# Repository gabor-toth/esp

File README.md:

Links:
  * https://docs.espressif.com/projects/esp-idf/en/latest/esp32/get-started/linux-macos-setup.html#get-started-first-steps
  * https://github.com/espressif/idf-eclipse-plugin/blob/master/README.md#GettingStarted
  * https://docs.espressif.com/projects/esp-idf/en/v5.0/esp32s2/hw-reference/chip-series-comparison.html

Install
=======

```
sudo apt -y install bison ccache cmake curl dfu-util flex gperf libffi-dev libssl-dev libusb-1.0-0 
sudo apt -y install ninja-build python3 python-is-python3 python3-pip python3-setuptools python3-venv
#sudo apt-get install git wget 
#sudo apt-mark auto libusb-1.0-0 python3 python3-setuptools wget 
```

```
cd ~/own/projects
git clone --recursive https://github.com/espressif/esp-idf.git
cd esp-idf
./install.sh esp32 esp32s2
```

LVGL
----

 * https://github.com/lvgl/lv_port_esp32
 
```
cd esp-idf

git submodule add https://github.com/lvgl/lvgl.git components/lvgl
pushd components/lvgl
git checkout release/v8.3
popd

git submodule add https://github.com/lvgl/lvgl_esp32_drivers.git components/lvgl_esp32_drivers
```

NMEA2000
--------

In menuconfig check "Enable C++ extension" before adding the component

```
mkdir -p components
cd components
git submodule add https://github.com/ttlappalainen/NMEA2000
```

NPM
---

- https://github.com/nvm-sh/nvm

```
curl -o- https://raw.githubusercontent.com/nvm-sh/nvm/v0.40.3/install.sh | bash
# run it on a new terminal
nvm install 22 --save
```

NG
--

```
cd ~/projects/ecp/ontozo/frontend
npm install
npm link @angular/cli
```

Upgrade
=======

Upgrade esp-idf
---------------

```
pushd ../../esp-idf
git pull
git checkout v5.1.2
git submodule update --init --recursive
rm -rf $HOME/.espressif/
./install.sh esp32 esp32s2
. ./export.sh
cd tools
./idf_tools.py install cmake install-python-env
popd
```

Upgrade project in command line
-------------------------------

```
idf.py fullclean
idf.py menuconfig
idf.py build
```

Upgrade project in CLion
------------------------

  * ``echo $PATH``
  * Change IDF_PATH and PATH in CLion
  * File/Reload CMake project

Compile & more
==============

init.sh does this
```
. ~/own/projects/esp-idf/export.sh
```

Find out device

```
$ l /dev/ttyUSB*
crw-rw---- 1 root dialout 188, 0 ápr    5 20:01 /dev/ttyUSB0
sudo usermod -a -G dialout gabor
```

If there's no ttyUSB0
```
sudo apt remove brltty
```

New project
-----------

Copy init.sh, run it

```
. ./init.sh

idf.py set-target esp32s2
idf.py menuconfig
idf.py -p /dev/ttyUSB0 flash -b 3000000 monitor
```

In CLion
  * File, Open
  * CMakeLists.txt

Change target 
-------------

```
idf.py set-target esp32s2
rm -rf cmake-build-debug/
idf.py fullclean
```

Reload CMake project in CLion

Add managed components

```
idf.py add-dependency espressif/mdns
idf.py add-dependency espressif/mpu6050
idf.py add-dependency espressif/esp_websocket_client
idf.py build
```

Git
===

Use different SSL private key

```
export GIT_SSH_COMMAND="ssh -i $HOME/.ssh/id_gabtoth -o IdentitiesOnly=yes"
```

CLion
=====

CMake environment (Settings / Build, Execution, Deployment / CMake / Environment)

```
IDF_PATH=/home/gabor/projects/esp/esp-idf;PATH=home/gabor/projects/esp/esp-idf/components/espcoredump:/home/gabor/projects/esp/esp-idf/components/partition_table:/home/gabor/projects/esp/esp-idf/components/app_update:/home/gabor/.espressif/tools/xtensa-esp-elf-gdb/14.2_20240403/xtensa-esp-elf-gdb/bin:/home/gabor/.espressif/tools/xtensa-esp-elf/esp-14.2.0_20241119/xtensa-esp-elf/bin:/home/gabor/.espressif/tools/riscv32-esp-elf/esp-14.2.0_20241119/riscv32-esp-elf/bin:/home/gabor/.espressif/tools/esp32ulp-elf/2.38_20240113/esp32ulp-elf/bin:/home/gabor/.espressif/tools/cmake/3.30.2/bin:/home/gabor/.espressif/tools/openocd-esp32/v0.12.0-esp32-20250226/openocd-esp32/bin:/home/gabor/.espressif/python_env/idf5.4_py3.12_env/bin:/home/gabor/projects/esp/esp-idf/tools:/usr/local/sbin:/usr/local/bin:/usr/sbin:/usr/bin:/sbin:/bin:/usr/games:/usr/local/games:/snap/bin:/snap/bin
```

Windows
-------

```
[Environment]::GetEnvironmentVariable("IDF_PATH")
$Env:Path
python C:\Espressif\frameworks\esp-idf-v5.2.1-2\tools\idf_tools.py install-python-env
```

Something else

```
PATH += /home/tothg/.espressif/tools/xtensa-esp32-elf/esp-2021r2-patch3-8.4.0/xtensa-esp32-elf/bin:/home/tothg/.espressif/tools/xtensa-clang/12.0.1-d9341b81fc/xtensa-esp32-elf-clang/bin:/home/tothg/.espressif/tools/esp32ulp-elf/2.28.51-esp-20191205/esp32ulp-elf-binutils/bin:/home/tothg/.espressif/tools/cmake/3.20.3/bin:/home/tothg/.espressif/tools/openocd-esp32/v0.11.0-esp32-20211220/openocd-esp32/bin:/home/tothg/.espressif/tools/ninja/1.10.2/:/home/tothg/.espressif/python_env/idf5.0_py3.8_env/bin:/home/gabor/projects/esp-idf/tools:
IDF_PATH = /home/gabor/projects/esp-idf
```

USB on Windows
--------------

- https://blog.manzelseet.com/fixing-cp2102-with-custom-vidpid.html
- https://community.silabs.com/s/article/downloading-cp210x-drivers-from-windows-update?language=en_US
  The PIDs that must be programmed to the CP210x device are listed below: 0x10C4 0xEA63
- https://github.com/DiUS/cp210x-cfg/blob/master/README.md
- https://blog.manzelseet.com/fixing-cp2102-with-custom-vidpid.html
- https://community.silabs.com/s/question/0D51M00007xeNnTSAU/an721-cp21xxcustomizationutilityexe-not-found?language=en_US

Hardware
========

Display
-------

  * https://electropeak.com/learn/interfacing-2-8-inch-tft-lcd-touch-screen-with-esp32/
  * http://www.lcdwiki.com/2.8inch_SPI_Module_ILI9341_SKU:MSP2807

KiCad
=====

* search parts: https://componentsearchengine.com/
* library loader: https://componentsearchengine.com/ga/libraryLoaderSetup.php?flow=ll

links
* https://ms.componentsearchengine.com/library/kicad

TODO
====

fatal: remote error: upload-pack: not our ref 04b38e68fdf662cc866fca628e3e67a9714209d1
fatal: remote error: upload-pack: not our ref e1ba2bd2f61cd81c16b31b09772967fbfd72edd2
fatal: remote error: upload-pack: not our ref 11aa66e7f39c9402039882acb14a993e390f8893
fatal: remote error: upload-pack: not our ref 848df55b08dcdad33c7dd9dbc25deacd2fc5e489
fatal: remote error: upload-pack: not our ref 30e5c4f95bff1a17e06ce1042a165b0aa2bc4ca5
Errors during submodule fetch:
	components/lwip/lwip
	components/esp_wifi/lib
	components/bt/controller/lib_esp32h2/esp32h2-bt-lib
	components/bt/controller/lib_esp32c6/esp32c6-bt-lib
	components/bt/controller/lib_esp32c2/esp32c2-bt-lib

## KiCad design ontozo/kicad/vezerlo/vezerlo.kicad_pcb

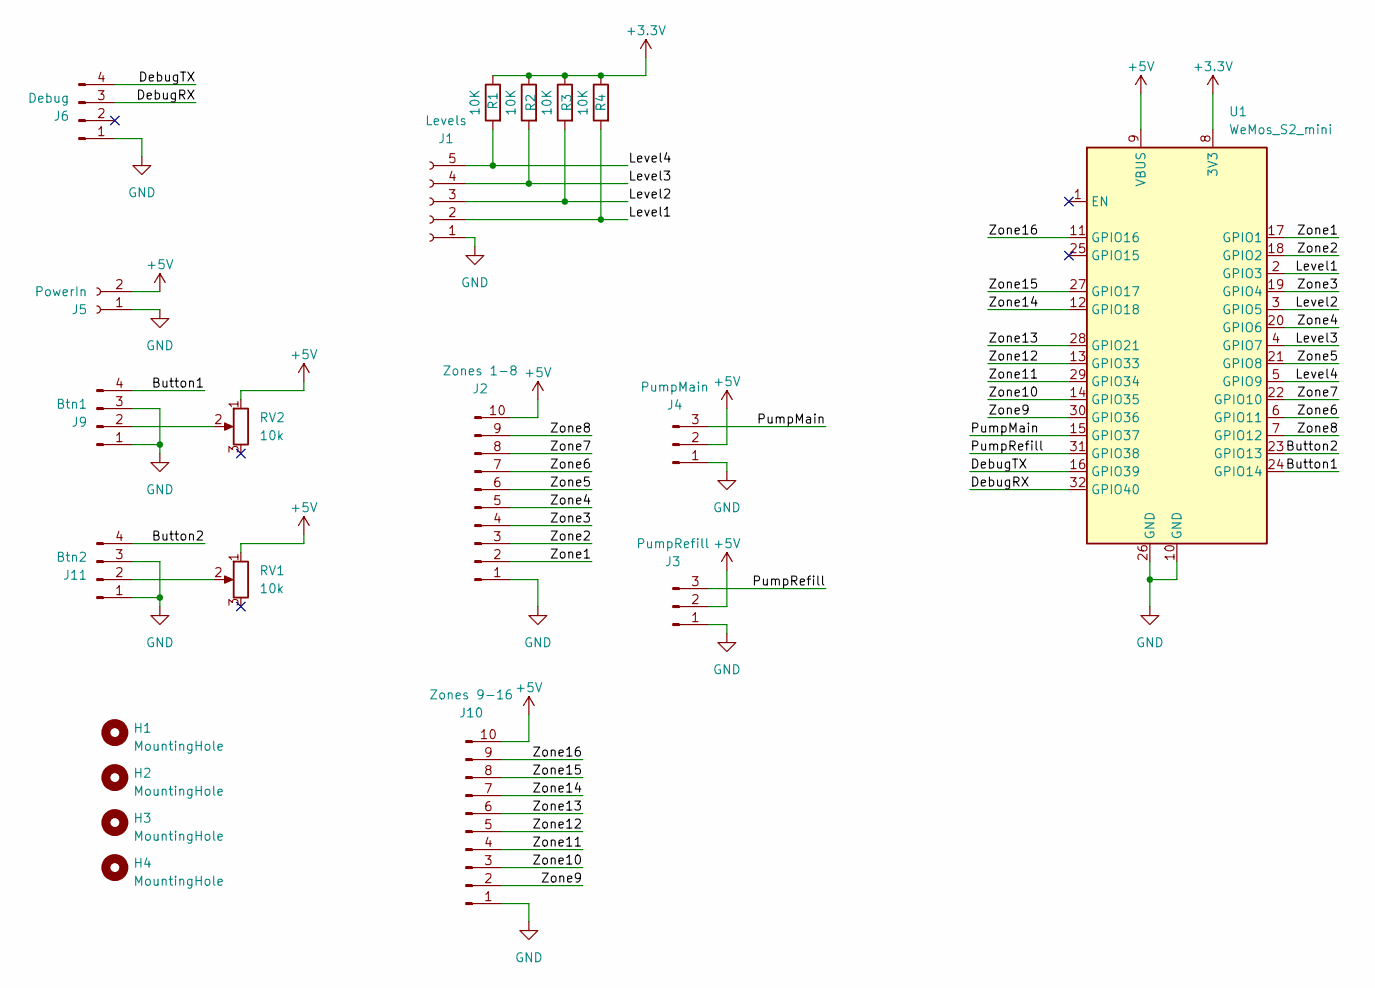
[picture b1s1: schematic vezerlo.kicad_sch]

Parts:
H1, H2, H3, H4: MountingHole; MountingHole_3.2mm_M3
J1: Levels; TerminalBlock_Phoenix_MKDS-1,5-5-5.08_1x05_P5.08mm_Horizont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
J2: Zones 1-8; PinHeader_1x10_P2.54mm_Vertical
J3: PumpRefill; PinHeader_1x03_P2.54mm_Vertical
J4: PumpMain; PinHeader_1x03_P2.54mm_Vertical
J5: PowerIn; TerminalBlock_Phoenix_MKDS-1,5-2-5.08_1x02_P5.08mm_Horizont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
J6: Debug; PinHeader_1x04_P2.54mm_Vertical
J9: Btn1; TerminalBlock_Phoenix_MKDS-1,5-4-5.08_1x04_P5.08mm_Horizont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
J10: Zones 9-16; PinHeader_1x10_P2.54mm_Vertical
J11: Btn2; TerminalBlock_Phoenix_MKDS-1,5-4-5.08_1x04_P5.08mm_Horizont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
R1, R2, R3, R4: 10K; R_Axial_DIN0207_L6.3mm_D2.5mm_P7.62mm_Horizontal
RV1, RV2: 10k; Potentiometer_Bourns_3386P_Vertical
U1: WeMos_S2_mini; WEMOS_S2_mini_gogo

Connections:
+3.3V: R1.1, R2.1, R3.1, R4.1, U1.8 (3V3)
+5V: J2.10, J3.2, J4.2, J5.2, J10.10, RV1.1, RV2.1, U1.9 (VBUS)
/Button1: J9.4, U1.24 (GPIO14)
/Button2: J11.4, U1.23 (GPIO13)
/DebugRX: J6.3, U1.32 (GPIO40)
/DebugTX: J6.4, U1.16 (GPIO39)
/Level1: J1.2, R4.2, U1.2 (GPIO3)
/Level2: J1.3, R3.2, U1.3 (GPIO5)
/Level3: J1.4, R2.2, U1.4 (GPIO7)
/Level4: J1.5, R1.2, U1.5 (GPIO9)
/PumpMain: J4.3, U1.15 (GPIO37)
/PumpRefill: J3.3, U1.31 (GPIO38)
/Zone1: J2.2, U1.17 (GPIO1)
/Zone2: J2.3, U1.18 (GPIO2)
/Zone3: J2.4, U1.19 (GPIO4)
/Zone4: J2.5, U1.20 (GPIO6)
/Zone5: J2.6, U1.21 (GPIO8)
/Zone6: J2.7, U1.6 (GPIO11)
/Zone7: J2.8, U1.22 (GPIO10)
/Zone8: J2.9, U1.7 (GPIO12)
/Zone9: J10.2, U1.30 (GPIO36)
/Zone10: J10.3, U1.14 (GPIO35)
/Zone11: J10.4, U1.29 (GPIO34)
/Zone12: J10.5, U1.13 (GPIO33)
/Zone13: J10.6, U1.28 (GPIO21)
/Zone14: J10.7, U1.12 (GPIO18)
/Zone15: J10.8, U1.27 (GPIO17)
/Zone16: J10.9, U1.11 (GPIO16)
GND: J1.1, J2.1, J3.1, J4.1, J5.1, J6.1, J9.1, J9.3, J10.1, J11.1, J11.3, U1.10 (GND), U1.26 (GND)
unnamed: J9.2, RV2.2
unnamed: J11.2, RV1.2

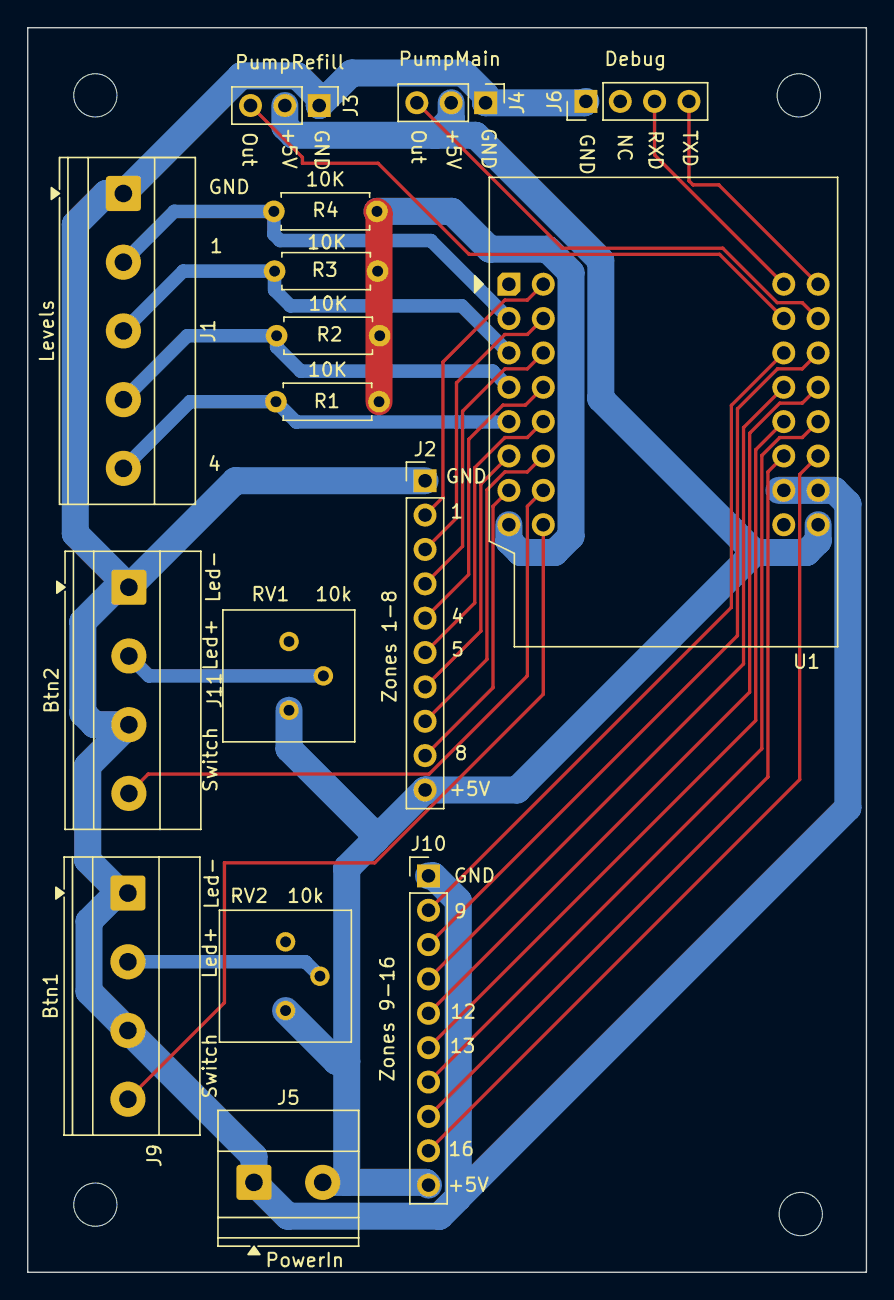
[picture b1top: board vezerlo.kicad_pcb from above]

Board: 2 copper layers, 62.0 x 92.0 mm, 20 parts (0 on the bottom side), 31 nets.

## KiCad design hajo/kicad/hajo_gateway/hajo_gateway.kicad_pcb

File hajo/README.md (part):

# Signal K

- https://signalk.org/installation.html
    - https://demo.signalk.org/@signalk/instrumentpanel/
- https://github.com/SignalK/signalk-server#how-to-get-signal-k-server
- https://github.com/SignalK/signalk-server/blob/master/docker/README.md#quickstart

# Raspberry PI

## Install

### System

- download Raspberry PI Imager from here: https://www.raspberrypi.com/software/
- choose 'Raspberry PI OS (other)', then choose 'OS Lite (64 bit)'
- (which will download an image from
  here https://www.raspberrypi.com/software/operating-systems/#raspberry-pi-os-64-bit)
- select target SD card and write
- put SD card into PI, boot with HDMI and keyboard connected
- select Hungarian layout and normal keyboard
- set hostname to 'signalk'
- create user 'signalk' with password 'signalk'
- login with those credentials
- set up ssh server

```shell
sudo raspi-config
```

- then go to menu 3 'Interfaces' and I1 'SSH'
- and enable it
- connect from your pc

```shell
ssh signalk@192.168.72.191
```

- and continue in ssh

```shell
mkdir -p .ssh
chmod 700 .ssh/
echo 'ssh-ed25519 AAAAC3NzaC1lZDI1NTE5AAAAIKcyI/bADRtxOoJ1hDOtbntHil+7zQbVbTIEuEyCPMNb gabor.toth@p92.hu' > .ssh/authorized_keys

sudo su
apt -y update
apt -y upgrade
apt -y install lsb-release traceroute vim
sed -i 's/raspberrypi/solpi/' /etc/hosts
hostnamectl set-hostname solpi
sed -i '/history-search/ s/# //' /etc/inputrc
dpkg-reconfigure tzdata
# unattended-upgrades
# dpkg-reconfigure --priority=low unattended-upgrades
# raspi-config
 # ?
exit
exit
```

### Upgrade

Determine current version

```shell
lsb_release -a
cat /etc/debian_version 
```

Upgrade system

```shell
systemctl stop signalk
systemctl stop signalk.socket
systemctl stop shewllinabox

apt update
apt full-upgrade
```

Upgrade firmware

```shell
rpi-update
chmod -x /etc/cron.d/hotspot 
reboot
chmod +x /etc/cron.d/hotspot
```

### Power

- LED & HDMI: https://www.jeffgeerling.com/blogs/jeff-geerling/controlling-pwr-act-leds-raspberry-pi
- https://linuxhint.com/tips-tricks-optimize-power-consumption-raspberry-pi/
- https://raspberrypi.stackexchange.com/questions/114422/what-is-the-minimum-power-required-for-an-rpi-4-in-halt-or-shutdown/114423#114423

TODO: add commands

#### Tweak hardware settings

- https://linuxhint.com/tips-tricks-optimize-power-consumption-raspberry-pi/

```shell
sudo su
vi /boot/firmware/config.txt

# power save stuff
arm_boost=0
dtoverlay=disable-bt
# Turn off Power LED
dtparam=pwr_led_trigger=default-on
dtparam=pwr_led_activelow=off
# Turn off Activity LED
dtparam=act_led_trigger=none
dtparam=act_led_activelow=off
# Turn off Ethernet ACT LED
dtparam=eth_led0=4
# Turn off Ethernet LNK LED
dtparam=eth_led1=4

# clock is not stable below 600
arm_freq_min=600
core_freq_min=100
sdram_freq_min=50
over_voltage_min=0
```

Bluetooth

```shell
systemctl stop bluetooth
systemctl disable bluetooth
```

Startup speed

```shell
systemd-analyze blame
```

### SignalK

Source link?

```shell
sudo su
# install v18 on bookworm (needed for Zero)
apt -y install nodejs npm
# install latest (v22 at the time being)
curl -fsSL https://deb.nodesource.com/setup_20.x | bash -
apt -y install nodejs
# continue for all
apt -y install libnss-mdns avahi-utils libavahi-compat-libdnssd-dev
apt-mark auto libnss-mdns
npm install -g npm@latest
npm install -g --unsafe-perm signalk-server -y # will take a while
signalk-server-setup
# Enter the location to store server configuration: /home/signalk/.signalk
# Enter your vessel name: sol
# Enter your mmsi if you have one: 
# The Signal K default port is 3000
# Port 80 does not require ":3000" in the browser and app interfaces
# Do you want to use port 80? Yes
# Do you want to enable SSL? No

cat >>/etc/systemd/system/signalk.service <<EOF
[Unit]
Wants=network.target
EOF
systemctl daemon-reload
```

For local debugging

```
npm install --unsafe-perm signalk-server -y
./node_modules/.bin/signalk-server-setup
/home/apa/.signalk/signalk-server
#/usr/bin/node --inspect ...
```

#### Canboat

```shell
sudo raspi-config
```

- Interface Options
- Serial Port
- No (login shell)
- Yes (serial)
- Reboot

https://github.com/canboat/canboat/wiki/Building

```shell
sudo apt -y install git
git clone https://github.com/canboat/canboat
# or
git pull
cd canboat
make
sudo make install

sudo usermod -a -G dialout signalk
# log out and in
actisense-serial -d /dev/ttyAMA0
```

- Server
- Data connections
- type: NMEA 2000, id: n2k
- source: Actisense NGT-1 (canboat), port /dev/ttyAMA0, baud 115200

#### Dashboard

- go to http://192.168.72.191/
- create an admin account admin/signalk
- login
- Install from Appstore
    - mandatory
        - @mxtommy/kip (https://github.com/mxtommy/Kip)
        - @signalk/freeboard-sk
        - @signalk/charts-plugin
        - @signalk/course-provider
        - @signalk/set-system-time
        - signalk-alarm-silencer
        - signalk-derived-data (https://github.com/SignalK/signalk-derived-data/blob/master/README.md)
        - signalk-racing-calculator
        - signalk-generic-pgn-parser
        - optional
            - signalk-fixed-position
            - @signalk/signalk-autopilot
            - rest-provider-signalk (https://www.npmjs.com/package/rest-provider-signalk)
- Derived data
    - Engines: main
    - Batteries: 0,1,2
    - Heading: Magnetic Variation
    - Submit
    - Heading: True Heading
    - Course data
        - Course DTG, XTE, BRG, etc
        - Velocity Made Good towards next waypoint
        - Velocity Made Good to wind
    - optional
        - Wind: Wind shift
- Course Data provider
    - GreatCircle
- Setup
    - Server,Settings, Options, mdns enable
    - Save, restart
- Create user kip, set pwd kip, admin or at least r/w
- Link: http://192.168.72.156/@mxtommy/kip
- Copy demo page to local user
    - load demo
    - menu Configuration, Settings,
    - connect to local, don't log in,
    - request token, approve in SignalK (timeout = NEVER)
    - go to Storage tab, save layout to global/default
    - go to SignalK tab, log in with kip/kip
    - go to Storage tab, copy remote global/default to remote user/default
- offline maps
    - see https://pysselilivet.blogspot.com/2021/09/signal-k-charts-offline-online.html
      ```shell
      cd ~/.signalk/charts
      wget https://ftp.gwdg.de/pub/misc/openstreetmap/openseamap/charts/mbtiles/OSM-OpenCPN2-Lake_Balaton.mbtiles
      ```
    - click Submit in "Signal K Charts" plugin
    - check results: http://192.168.72.156/signalk/v2/api/resources/charts
- heartbneat
    - configure signalk-generic-pgn-parser
- todo
    - self.electrical.batteries.1.voltage

### Amend PGNs in Signalk

Check whether PGN definition is there

- /usr/lib/node_modules/signalk-server/node_modules/@canboat/pgns/canboat.json
- /usr/lib/node_modules/signalk-server/node_modules/@canboat/pgns/pgns.json
- /usr/lib/node_modules/signalk-server/node_modules/@canboat/pgns/canboat.json

Implement mapper here

- /usr/lib/node_modules/signalk-server/node_modules/@signalk/n2k-signalk/n2kMapper.js
- /usr/lib/node_modules/signalk-server/node_modules/@signalk/n2k-signalk/raymarine/index.js
- /usr/lib/node_modules/signalk-server/node_modules/@signalk/n2k-signalk/raymarine/129029.js

### SignalK plugin development

See

- development: https://demo.signalk.org/documentation/develop/plugins/server_plugin.html
- npm link: https://docs.npmjs.com/cli/v9/commands/npm-link

```shell
cd projects/signalk-generic-pgn-parser
sudo npm link
cd ~/.signalk/
npm link signalk-generic-pgn-parser
```

### Wifi AP

On Debian 12 (Bookworm), see https://raspberrytips.com/access-point-setup-raspberry-pi/

```shell
raspi-config
  Localization, Wifi country, HU, Finish
nmcli con add con-name hotspot ifname wlan0 type wifi ssid "sol"
nmcli con modify hotspot ipv4.method shared ipv4.address 192.168.77.1/24
nmcli con modify hotspot wifi-sec.key-mgmt wpa-psk
nmcli con modify hotspot wifi-sec.psk "SoL37695"
nmcli con modify hotspot 802-11-wireless.mode ap 802-11-wireless.band bg 802-11-wireless.channel 2 ipv4.method shared
nmcli con modify hotspot 802-11-wireless.channel 7
nmcli con modify hotspot 802-11-wireless-security.proto rsn

nmcli connection down hotspot
nmcli connection up hotspot
```

User interface

```shell
nmtui
```

### Wifi station

On Debian 12 (Bookworm):

```shell
nmcli dev show wlan0
nmcli dev wifi list
nmcli connection show

#nmcli dev set wlan1 autoconnect yes
nmcli dev wifi connect TothKiss password ******** ifname wlan0
nmcli dev wifi connect TGA password ******** ifname wlan0
#nmcli connection modify TothKiss connection.autoconnect yes

systemctl restart NetworkManager
```

Turn off Wifi dongle's LED:

- https://github.com/lwfinger/rtl8188eu/issues/82

```shell
echo 0 > /sys/class/leds/rtl8xxxu-usb1-1.4/brightness
```

See

- https://serverfault.com/questions/869857/systemd-how-to-selectively-disable-wpa-supplicant-for-a-specific-wlan-interface
- https://forums.raspberrypi.com/viewtopic.php?t=211853
- https://stackoverflow.com/questions/66514910/enable-predictable-network-interfaces-via-shell-on-raspberry-pi
- https://forums.raspberrypi.com/viewtopic.php?t=198946

### Others

#### Connect to box

```shell
ssh signalk@192.168.72.156
ssh signalk@192.168.77.1
```

#### Wifi Commands

```shell
sudo su
ip link set dev wlan0 down
ip link set dev wlan0 up
iwlist wlan0 scan
vi wpa_supplicant/wpa_supplicant.conf
wpa_supplicant -B -c /etc/wpa_supplicant/wpa_supplicant.conf -i wlan0
wpa_cli terminate -i wlan0
```

## Build

```shell
idf.py -p /dev/ttyUSB0 flash -b 3000000 -DCONFIG_DEVICE_TYPE=GATEWAY -DCONFIG_START_SIMULATOR=y
```

# Local testing

## In Docker

```shell
docker run -d --init  --name signalk-server -p 3000:3000 -v $(pwd):/home/node/.signalk cr.signalk.io/signalk/signalk-server
```

## Local

```shell
sudo apt isntall libavahi-compat-libdnssd-dev
sudo npm install -g mdns
sudo npm install -g signalk-server
```

## Requests

```shell
curl -X GET http://10.128.65.180:3000/signalk
{"endpoints":{"v1":{"version":"2.4.1","
signalk-http":"http://10.128.65.180:3000/signalk/v1/api/","signalk-ws":"ws://10.128.65.180:3000/signalk/v1/stream","signalk-tcp":"tcp://10.128.65.180:8375"}},"server":{"id":"signalk-server-node","version":"2.4.1"}}
```

```shell
wscat -c "ws://10.128.65.180:3000/signalk/v1/stream?subscribe=all"
Connected (press CTRL+C to quit)
< {"name":"signalk-server","version":"2.4.1","self":"vessels.urn:mrn:signalk:uuid:
59e1f1c9-9e32-4340-a1d0-656512c48f0a","roles":["master","main"],"timestamp":"2023-11-22T12:55:47.852Z"}
< {"context":"vessels.urn:mrn:signalk:uuid:59e1f1c9-9e32-4340-a1d0-656512c48f0a","updates":[{"$source":"defaults","
timestamp":"2023-11-22T12:43:36.969Z","
values":[{"path":"","value":{"uuid":"urn:mrn:signalk:uuid:59e1f1c9-9e32-4340-a1d0-656512c48f0a"}}]}]}
```

## Other links

- [Discovery and Connection Establishment](https://signalk.org/specification/1.7.0/doc/connection.html)
- [Streaming API](https://signalk.org/specification/1.7.0/doc/streaming_api.html)

## Service Sniffer

```shell
sudo apt install gssdp-tools

# MDNS
avahi-browse -r -a -t
avahi-browse -r _signalk-ws._tcp
avahi-browse -r _signalk-http._tcp

# SSDP
gssdp-device-sniffer -i docker0
gssdp-device-sniffer -i enp7s0
gssdp-device-sniffer -i wlp0s20f3
```

## URLs

http://192.168.72.182/description.xml
http://192.168.72.182/index.html
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
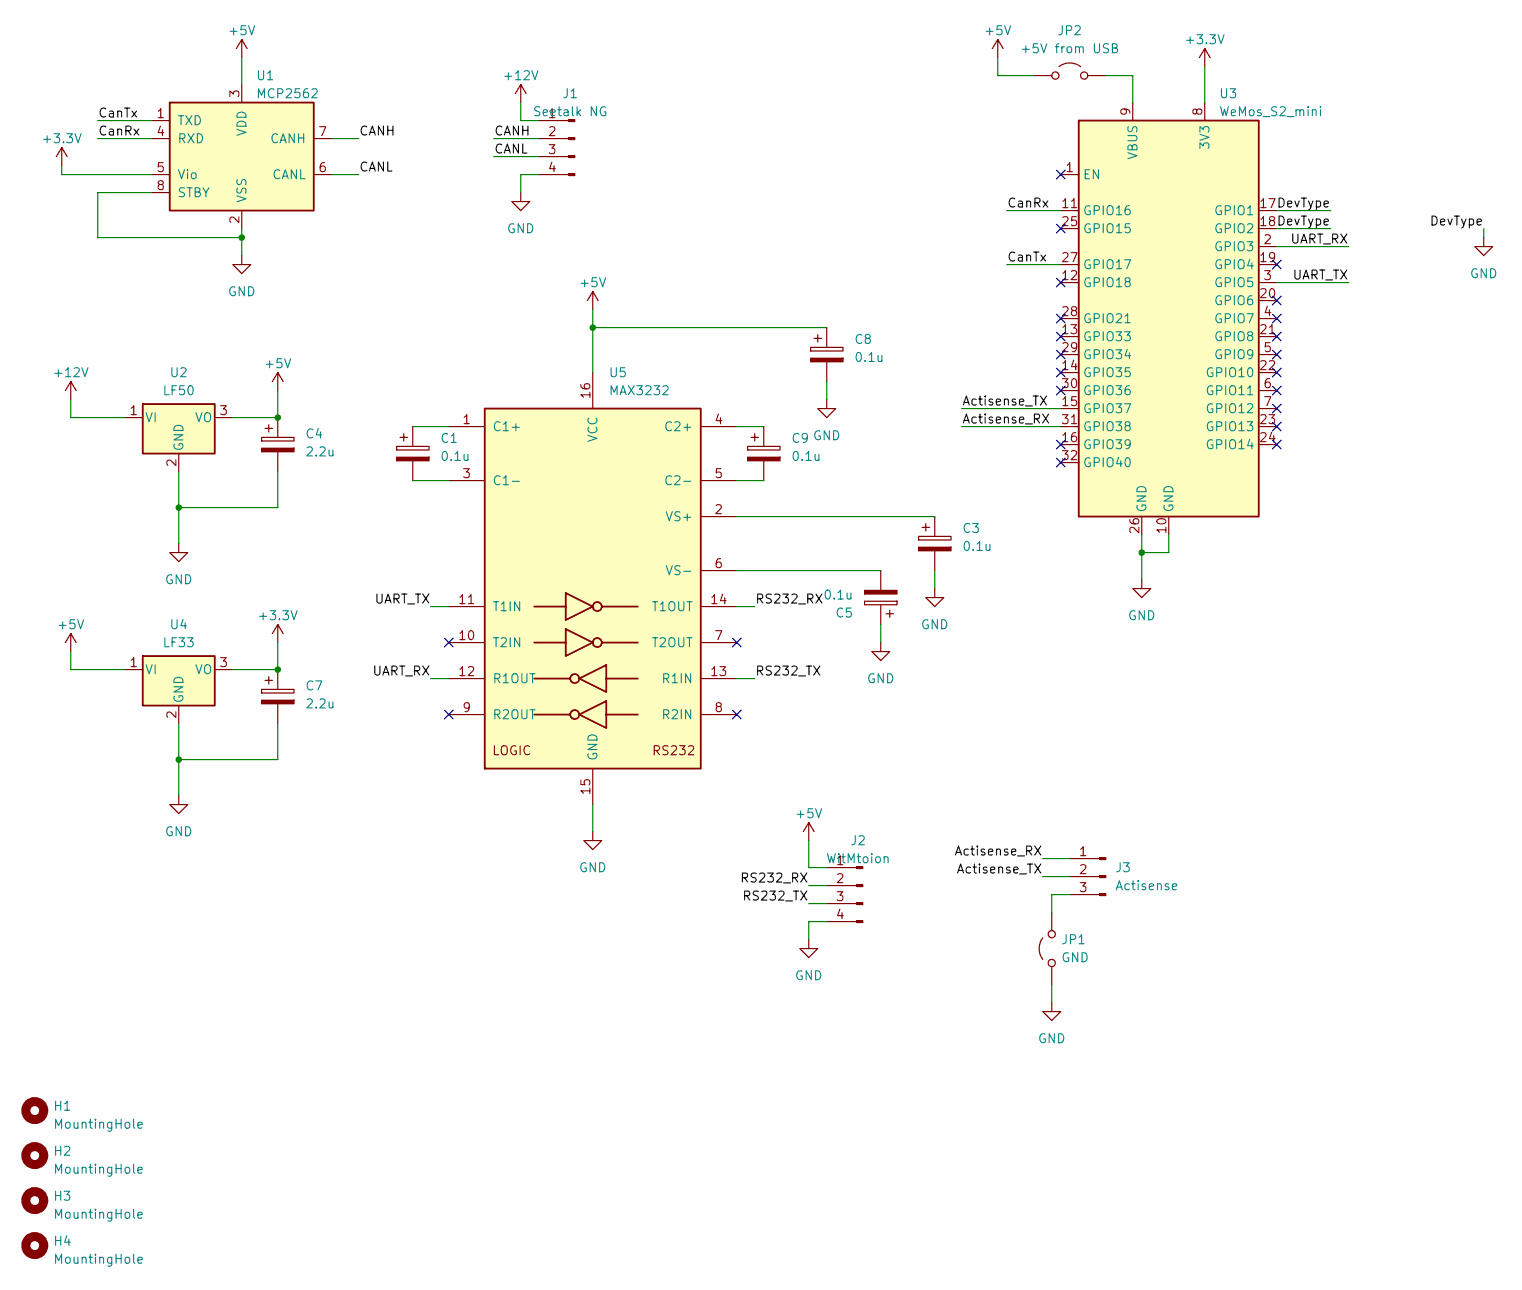
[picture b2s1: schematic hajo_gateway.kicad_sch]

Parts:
C1, C3, C5, C8, C9: 0.1u; CP_Radial_D5.0mm_P2.50mm
C4, C7: 2.2u; CP_Radial_D5.0mm_P2.00mm
H1, H2, H3, H4: MountingHole; MountingHole_3.2mm_M3
J1: Seetalk NG; JST_XA_B04B-XASK-1_1x04_P2.50mm_Vertical
J2: WitMtoion; JST_XA_B04B-XASK-1_1x04_P2.50mm_Vertical
J3: Actisense; JST_XH_B3B-XH-A_1x03_P2.50mm_Vertical
JP1: GND; PinHeader_1x03_P2.54mm_Vertical
JP2: +5V from USB; PinHeader_1x02_P2.54mm_Vertical
U1: MCP2562; DIP-8_W7.62mm_Socket
U2: LF50; TO-220-3_Vertical
U3: WeMos_S2_mini; WEMOS_S2_mini
U4: LF33; TO-220-3_Vertical
U5: MAX3232; DIP-16_W7.62mm_Socket

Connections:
+3.3V: C7.1, U1.5 (Vio), U3.8 (3V3), U4.3 (VO)
+5V: C4.1, C8.1, J2.1, JP2.1 (A), U1.3 (VDD), U2.3 (VO), U4.1 (VI), U5.16 (VCC)
+12V: J1.1, U2.1 (VI)
/Actisense_RX: J3.1, U3.31 (GPIO38)
/Actisense_TX: J3.2, U3.15 (GPIO37)
/CANH: J1.2, U1.7 (CANH)
/CANL: J1.3, U1.6 (CANL)
/CanRx: U1.4 (RXD), U3.11 (GPIO16)
/CanTx: U1.1 (TXD), U3.27 (GPIO17)
/RS232_RX: J2.2, U5.14 (T1OUT)
/RS232_TX: J2.3, U5.13 (R1IN)
/UART_RX: U3.2 (GPIO3), U5.12 (R1OUT)
/UART_TX: U3.3 (GPIO5), U5.11 (T1IN)
GND: C3.2, C4.2, C5.1, C7.2, C8.2, J1.4, J2.4, JP1.1 (A), U1.2 (VSS), U1.8 (STBY), U2.2 (GND), U3.10 (GND), U3.17 (GPIO1), U3.18 (GPIO2), U3.26 (GND), U4.2 (GND), U5.15 (GND)
unnamed: J3.3, JP1.2 (B)
unnamed: JP2.2 (B), U3.9 (VBUS)
unnamed: C1.1, U5.1 (C1+)
unnamed: C1.2, U5.3 (C1-)
unnamed: C9.1, U5.4 (C2+)
unnamed: C9.2, U5.5 (C2-)
unnamed: C3.1, U5.2 (VS+)
unnamed: C5.2, U5.6 (VS-)

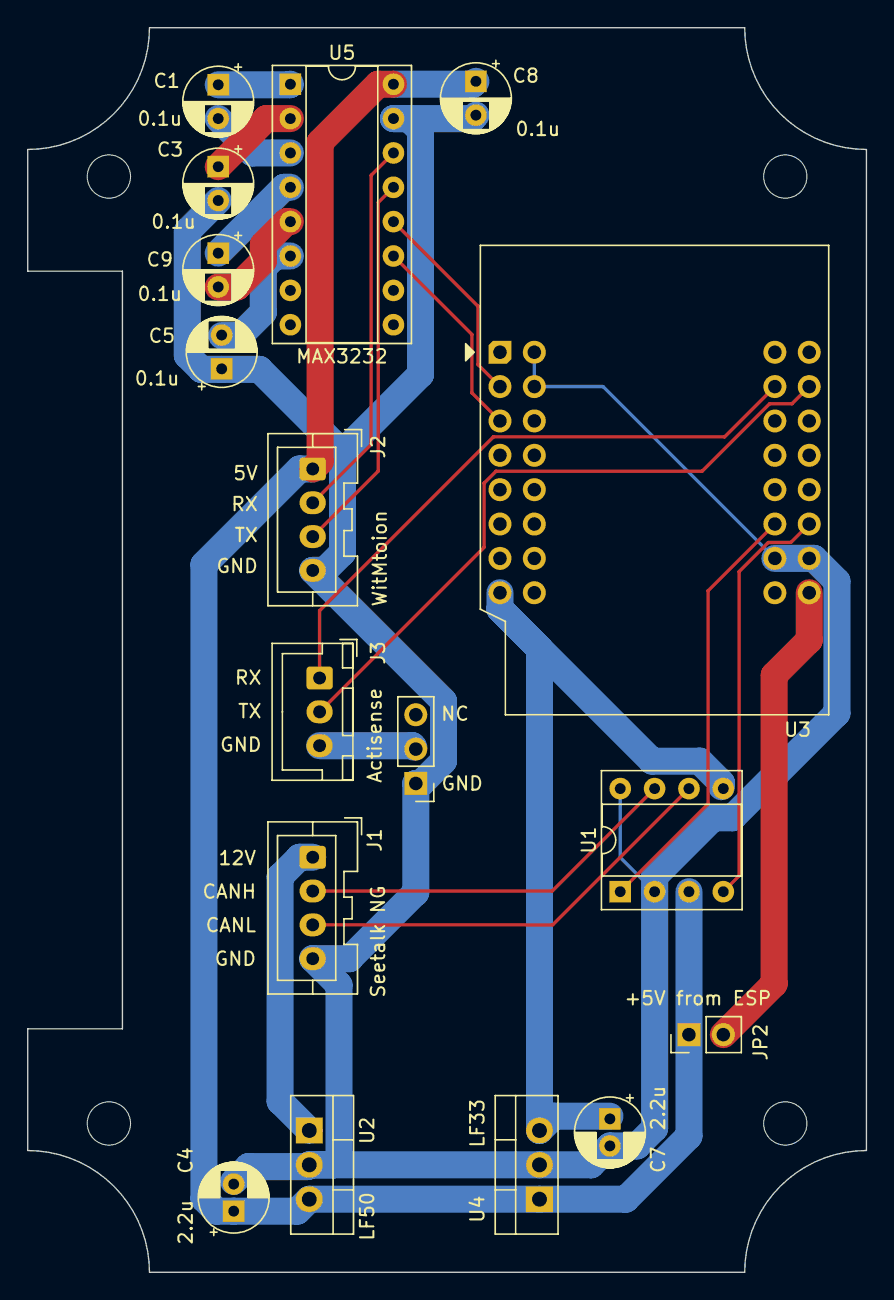
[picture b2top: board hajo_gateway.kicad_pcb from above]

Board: 2 copper layers, 62.0 x 92.0 mm, 21 parts (0 on the bottom side), 22 nets.

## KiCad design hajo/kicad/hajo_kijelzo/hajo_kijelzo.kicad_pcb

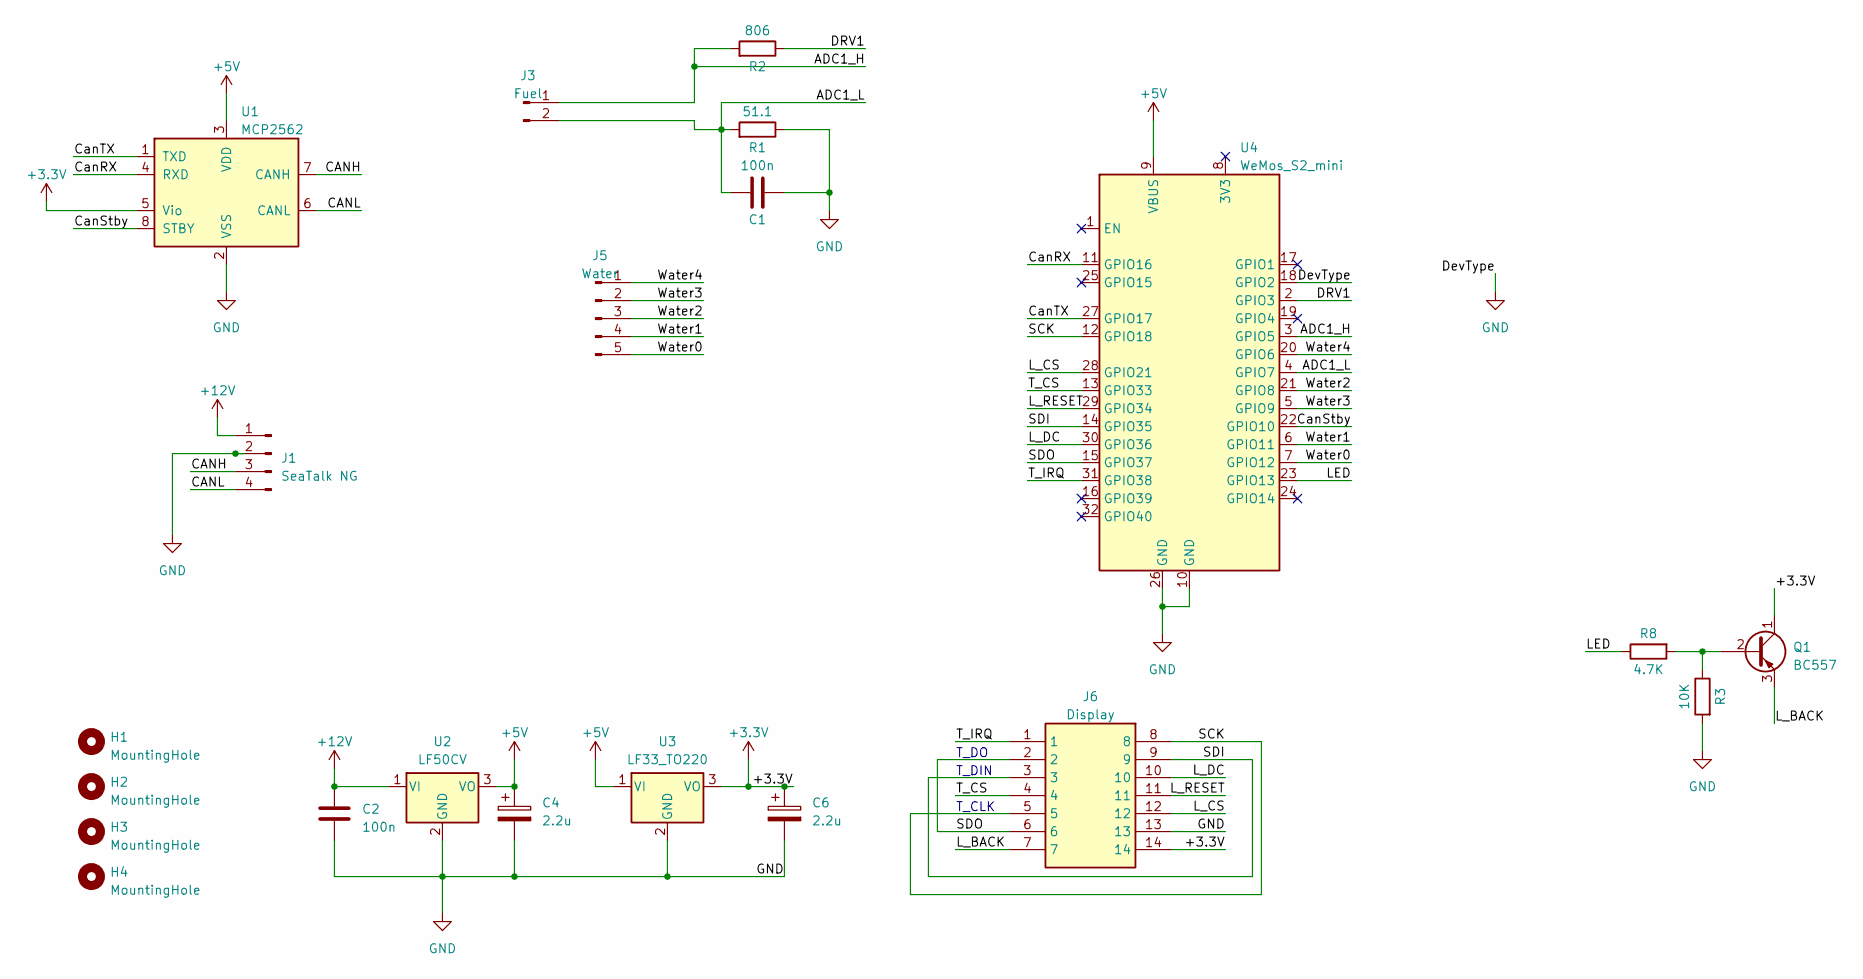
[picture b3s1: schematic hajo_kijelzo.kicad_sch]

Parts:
C1: 100n; C_Rect_L4.0mm_W2.5mm_P2.50mm
C2: 100n; C_Rect_L7.0mm_W2.0mm_P5.00mm
C4, C6: 2.2u; CP_Radial_D5.0mm_P2.00mm
H1, H2, H3, H4: MountingHole; MountingHole_3.2mm_M3
J1: SeaTalk NG; JST_XH_B4B-XH-A_1x04_P2.50mm_Vertical
J3: Fuel; 1821245
J5: Water; 1821274
J6: Display; 1844772; Manufacturer_Part_Number 1844772; Mouser Part Number 651-1844772
Q1: BC557; TO-92_Inline
R1: 51.1; R_Axial_DIN0207_L6.3mm_D2.5mm_P7.62mm_Horizontal
R2: 806; R_Axial_DIN0207_L6.3mm_D2.5mm_P7.62mm_Horizontal
R3: 10K; R_Axial_DIN0207_L6.3mm_D2.5mm_P7.62mm_Horizontal
R8: 4.7K; R_Axial_DIN0207_L6.3mm_D2.5mm_P7.62mm_Horizontal
U1: MCP2562; DIP-8_W7.62mm
U2: LF50CV; TO-220-3_Vertical
U3: LF33_TO220; TO-220-3_Vertical
U4: WeMos_S2_mini; WEMOS_S2_mini

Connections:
+3.3V: C6.1, J6.14, Q1.1 (C), U1.5 (Vio), U3.3 (VO)
+5V: C4.1, U1.3 (VDD), U2.3 (VO), U3.1 (VI), U4.9 (VBUS)
+12V: C2.1, J1.1, U2.1 (VI)
/ADC1_H: J3.1, R2.2, U4.3 (GPIO5)
/ADC1_L: C1.2, J3.2, R1.2, U4.4 (GPIO7)
/CANH: J1.3, U1.7 (CANH)
/CANL: J1.4, U1.6 (CANL)
/CanRX: U1.4 (RXD), U4.11 (GPIO16)
/CanStby: U1.8 (STBY), U4.22 (GPIO10)
/CanTX: U1.1 (TXD), U4.27 (GPIO17)
/DRV1: R2.1, U4.2 (GPIO3)
/LED: R8.1, U4.23 (GPIO13)
/L_BACK: J6.7, Q1.3 (E)
/L_CS: J6.12, U4.28 (GPIO21)
/L_DC: J6.10, U4.30 (GPIO36)
/L_RESET: J6.11, U4.29 (GPIO34)
/SCK: J6.5, J6.8, U4.12 (GPIO18)
/SDI: J6.3, J6.9, U4.14 (GPIO35)
/SDO: J6.2, J6.6, U4.15 (GPIO37)
/T_CS: J6.4, U4.13 (GPIO33)
/T_IRQ: J6.1, U4.31 (GPIO38)
/Water0: J5.5, U4.7 (GPIO12)
/Water1: J5.4, U4.6 (GPIO11)
/Water2: J5.3, U4.21 (GPIO8)
/Water3: J5.2, U4.5 (GPIO9)
/Water4: J5.1, U4.20 (GPIO6)
GND: C1.1, C2.2, C4.2, C6.2, J1.2, J6.13, R1.1, R3.2, U1.2 (VSS), U2.2 (GND), U3.2 (GND), U4.10 (GND), U4.18 (GPIO2), U4.26 (GND)
unnamed: Q1.2 (B), R3.1, R8.2

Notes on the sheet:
T_DO
T_DIN
T_CLK

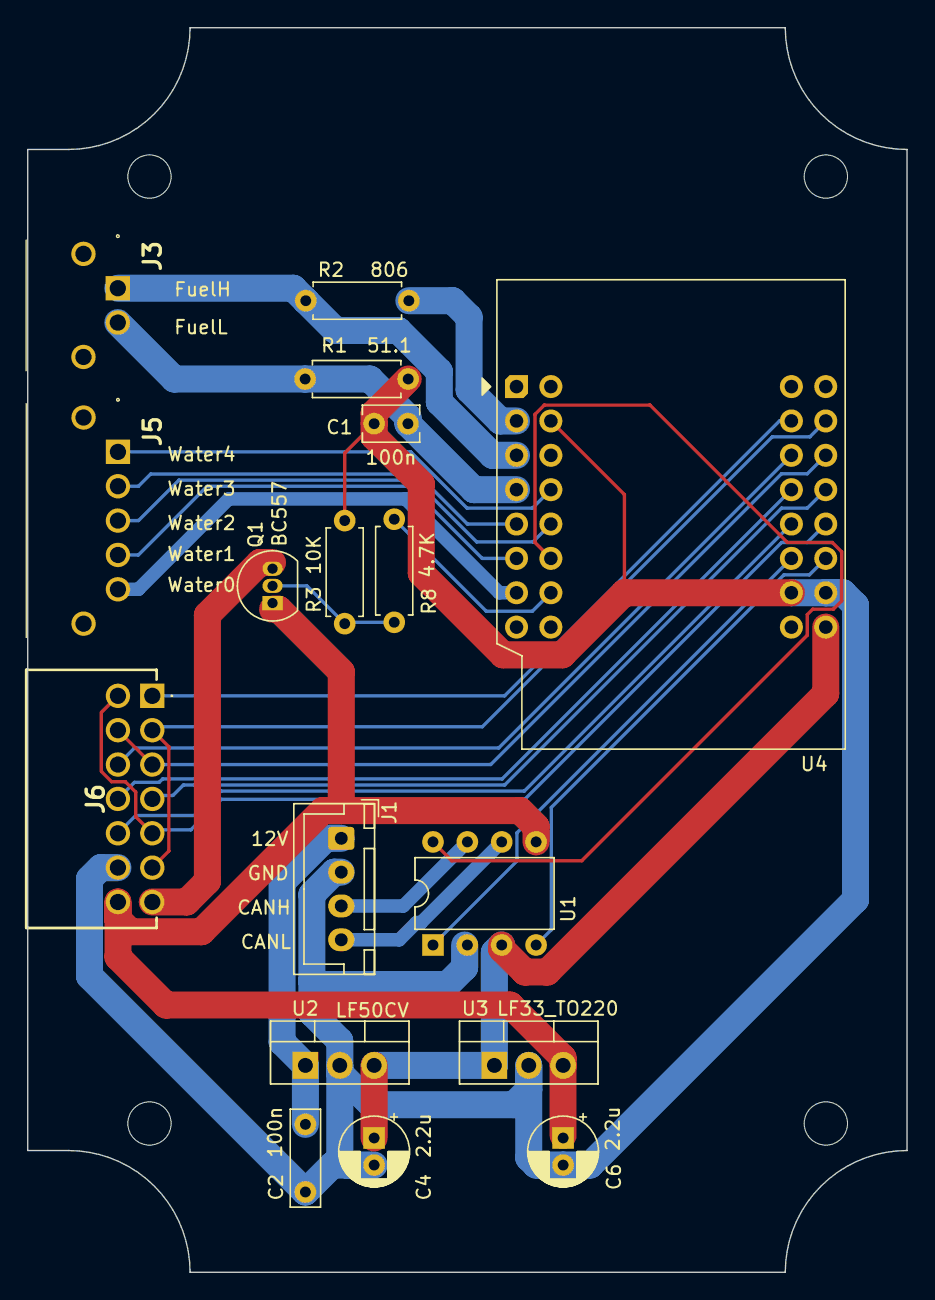
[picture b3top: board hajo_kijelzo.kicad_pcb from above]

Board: 2 copper layers, 65.0 x 92.0 mm, 21 parts (0 on the bottom side), 28 nets.

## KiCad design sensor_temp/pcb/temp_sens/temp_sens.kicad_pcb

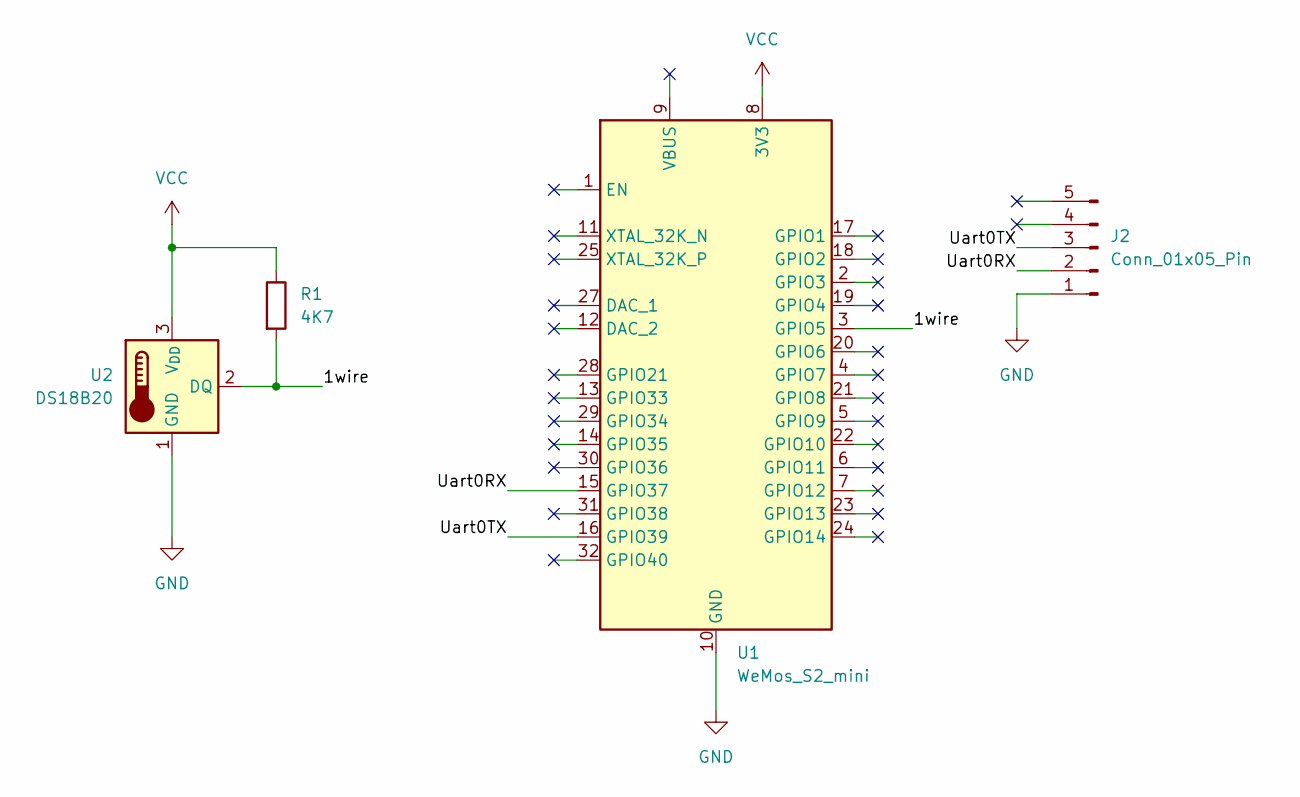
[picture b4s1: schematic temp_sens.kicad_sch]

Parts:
J2: Conn_01x05_Pin; PinHeader_1x05_P2.54mm_Horizontal
R1: 4K7; R_Axial_DIN0207_L6.3mm_D2.5mm_P10.16mm_Horizontal
U1: WeMos_S2_mini; WEMOS_S2_mini_traced
U2: DS18B20; TO-92_Inline

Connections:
/1wire: R1.2, U1.3 (GPIO5), U2.2 (DQ)
/Uart0RX: J2.2, U1.15 (GPIO37)
/Uart0TX: J2.3, U1.16 (GPIO39)
GND: J2.1, U1.10 (GND), U1.26 (GND), U2.1 (GND)
VCC: R1.1, U1.8 (3V3), U2.3 (V_{DD})

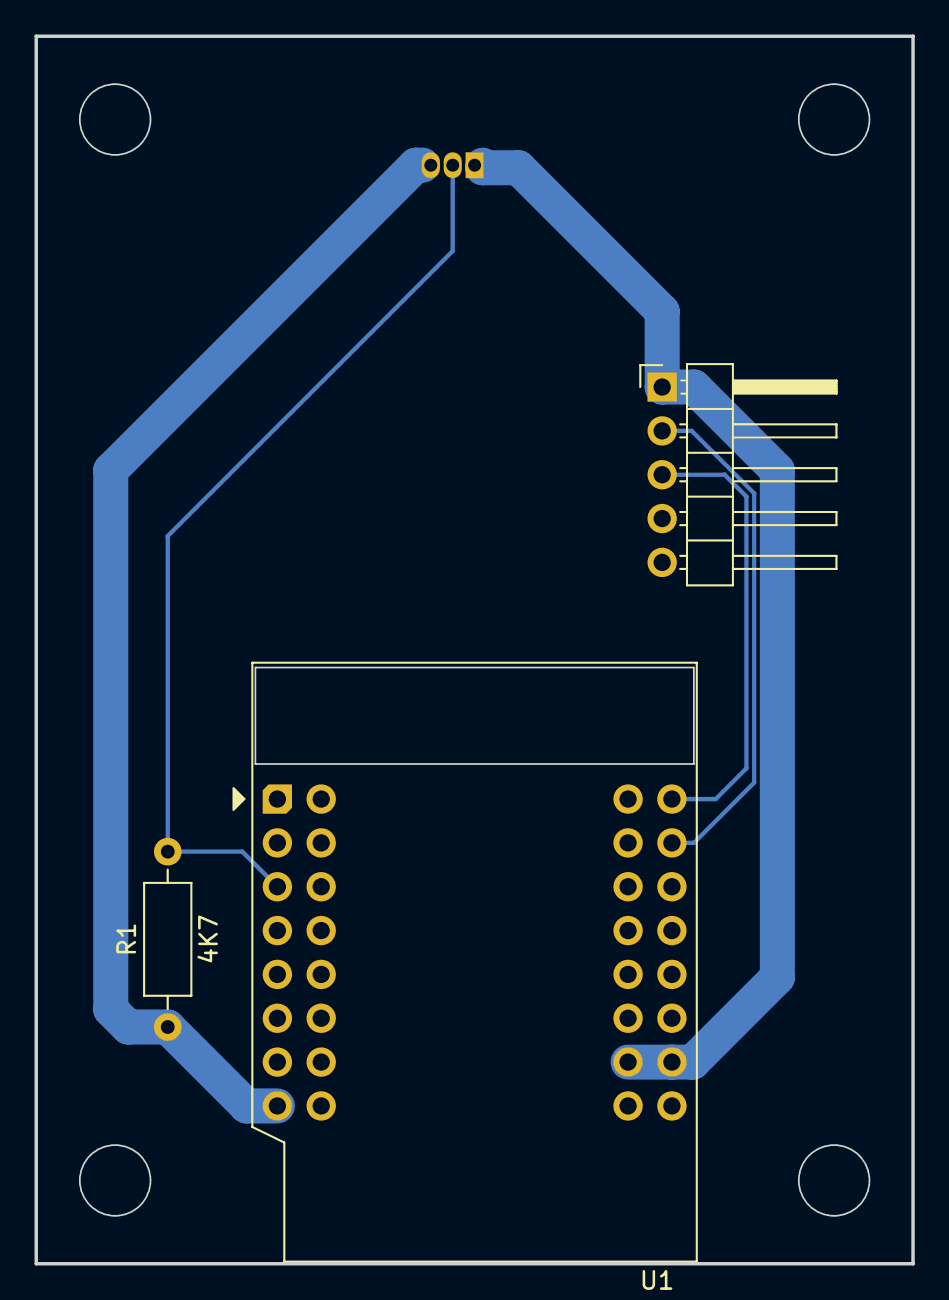
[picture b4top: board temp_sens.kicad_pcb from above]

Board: 2 copper layers, 50.8 x 71.1 mm, 4 parts (1 on the bottom side), 5 nets.

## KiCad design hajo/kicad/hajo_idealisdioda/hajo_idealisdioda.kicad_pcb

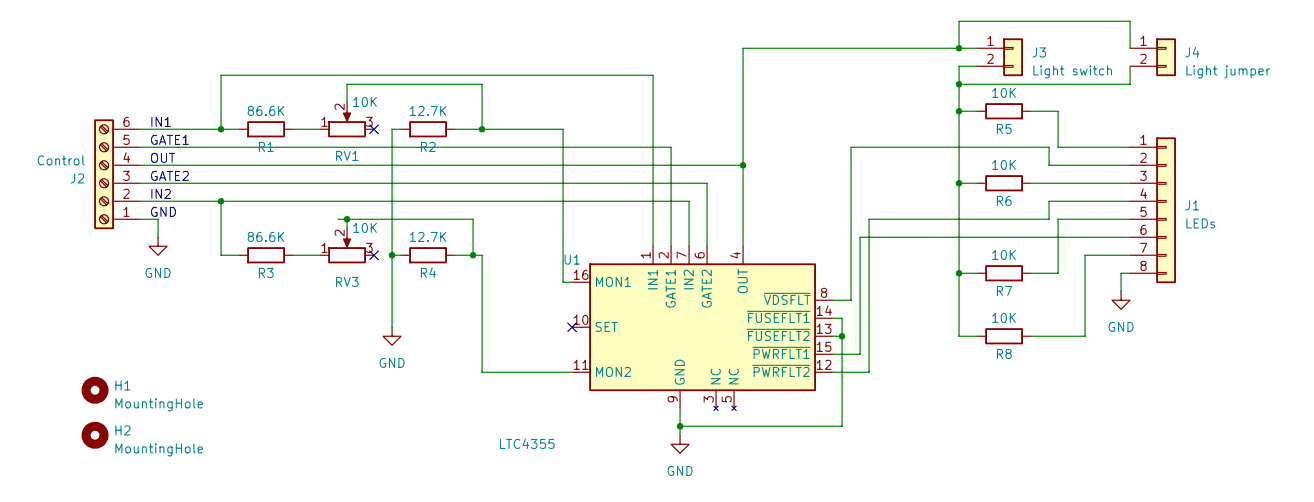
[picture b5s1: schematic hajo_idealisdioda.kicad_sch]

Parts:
H1, H2: MountingHole; MountingHole_2.5mm
J1: LEDs; PinHeader_1x08_P2.54mm_Vertical
J2: Control; PhoenixContact_MCV_1,5_6-G-5.08_1x06_P5.08mm_Vertical
J3: Light switch; PinHeader_1x02_P2.54mm_Vertical
J4: Light jumper; PinHeader_1x02_P2.54mm_Vertical
R1, R3: 86.6K; R_Axial_DIN0207_L6.3mm_D2.5mm_P7.62mm_Horizontal
R2, R4: 12.7K; R_Axial_DIN0207_L6.3mm_D2.5mm_P7.62mm_Horizontal
R5, R6, R7, R8: 10K; R_Axial_DIN0207_L6.3mm_D2.5mm_P7.62mm_Horizontal
RV1, RV3: 10K; PinHeader_1x03_P2.54mm_Vertical
U1: LTC4355; DIP-16_W7.62mm_Socket_LongPads

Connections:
GND: J1.8, J2.1, R2.2, R4.2, U1.9 (GND), U1.13 (~FUSEFLT2), U1.14 (~FUSEFLT1)
unnamed: J1.1, R5.2
unnamed: J1.2, U1.8 (~VDSFLT)
unnamed: J1.3, R6.2
unnamed: J1.4, U1.12 (~PWRFLT2)
unnamed: J1.5, R7.2
unnamed: J1.6, U1.15 (~PWRFLT1)
unnamed: J1.7, R8.2
unnamed: J2.2, R3.2, U1.7 (IN2)
unnamed: J2.3, U1.6 (GATE2)
unnamed: J2.4, J3.1, J4.1, U1.4 (OUT)
unnamed: J2.5, U1.2 (GATE1)
unnamed: J2.6, R1.2, U1.1 (IN1)
unnamed: J3.2, J4.2, R5.1, R6.1, R7.1, R8.1
unnamed: R1.1, RV1.1
unnamed: R3.1, RV3.1
unnamed: R2.1, RV1.2, U1.16 (MON1)
unnamed: R4.1, RV3.2, U1.11 (MON2)

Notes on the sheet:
IN1
IN2
GATE1
OUT
GND
GATE2

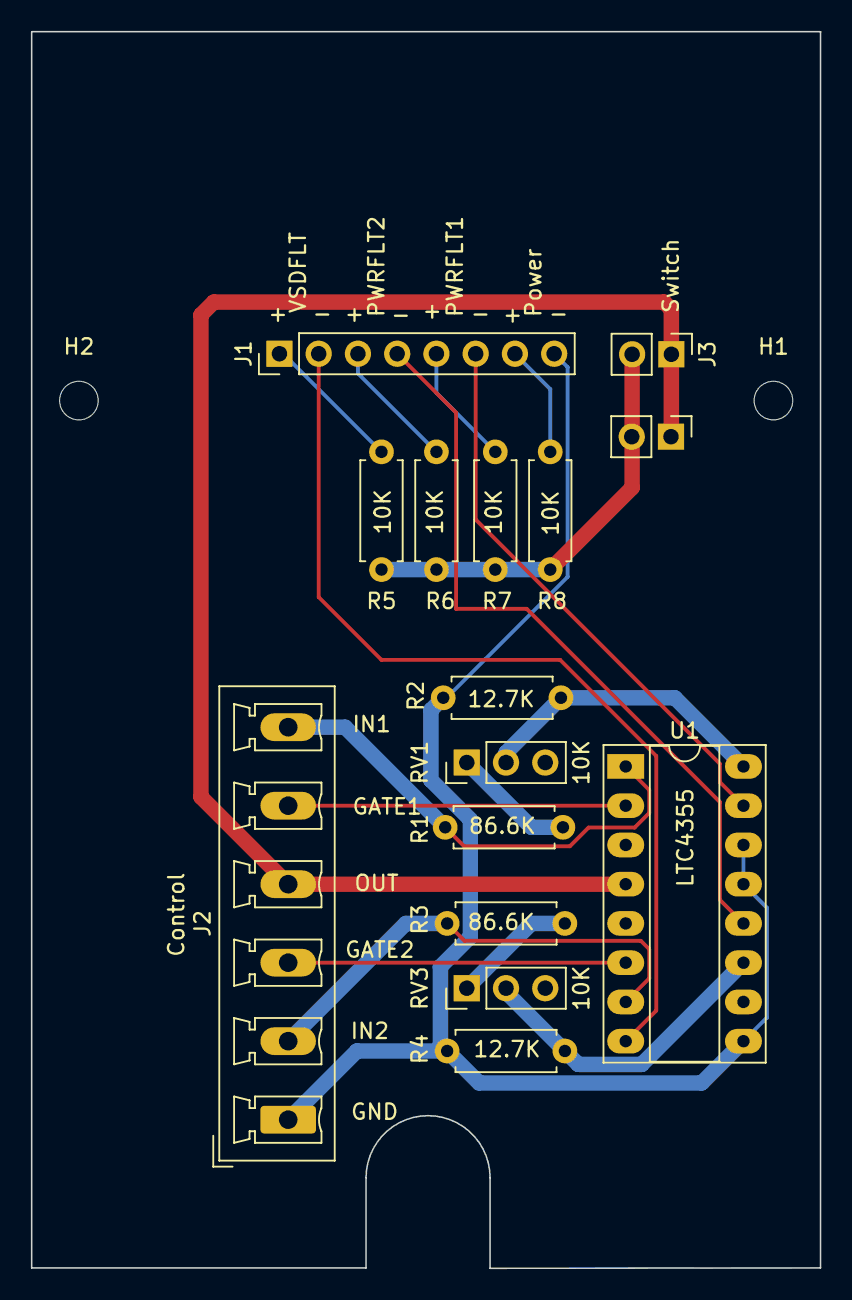
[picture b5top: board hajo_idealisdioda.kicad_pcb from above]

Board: 2 copper layers, 51.1 x 80.0 mm, 17 parts (0 on the bottom side), 18 nets.
